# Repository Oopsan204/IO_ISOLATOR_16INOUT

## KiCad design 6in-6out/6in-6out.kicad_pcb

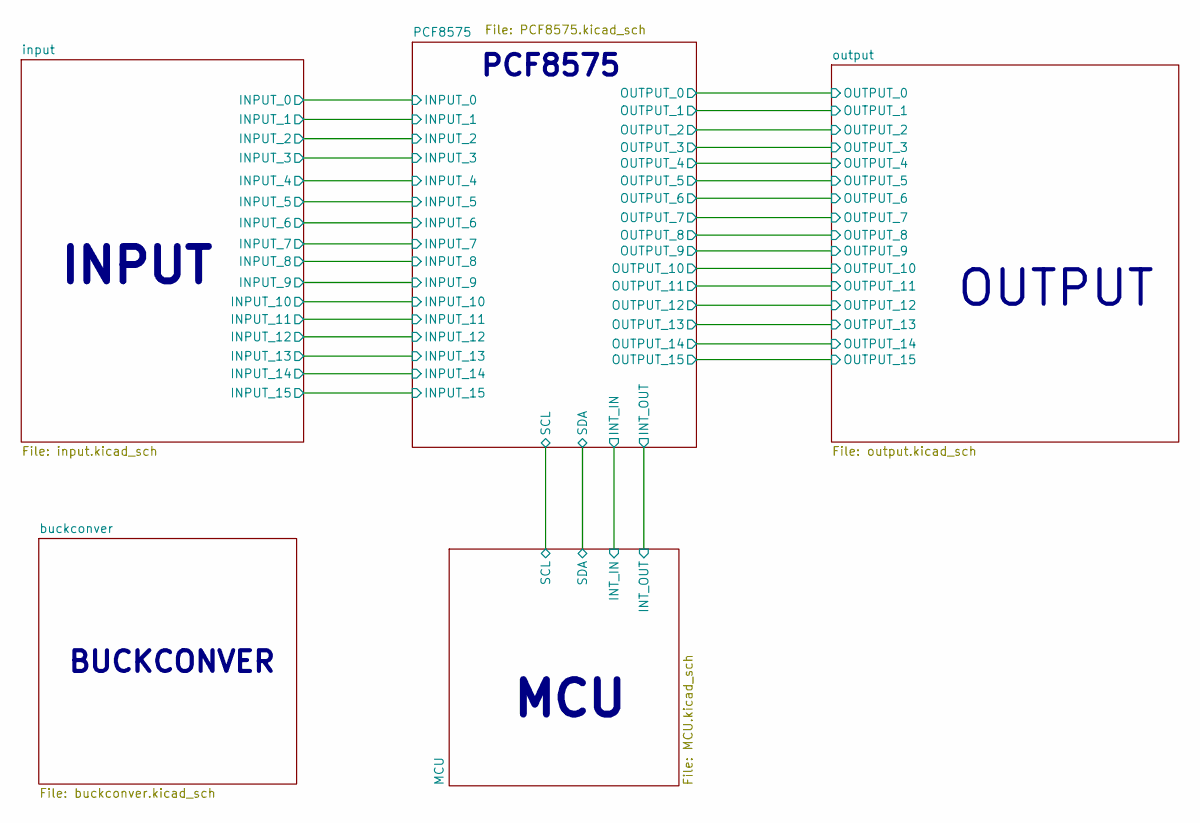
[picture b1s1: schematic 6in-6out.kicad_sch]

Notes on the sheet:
MCU
OUTPUT
PCF8575
INPUT
BUCKCONVER

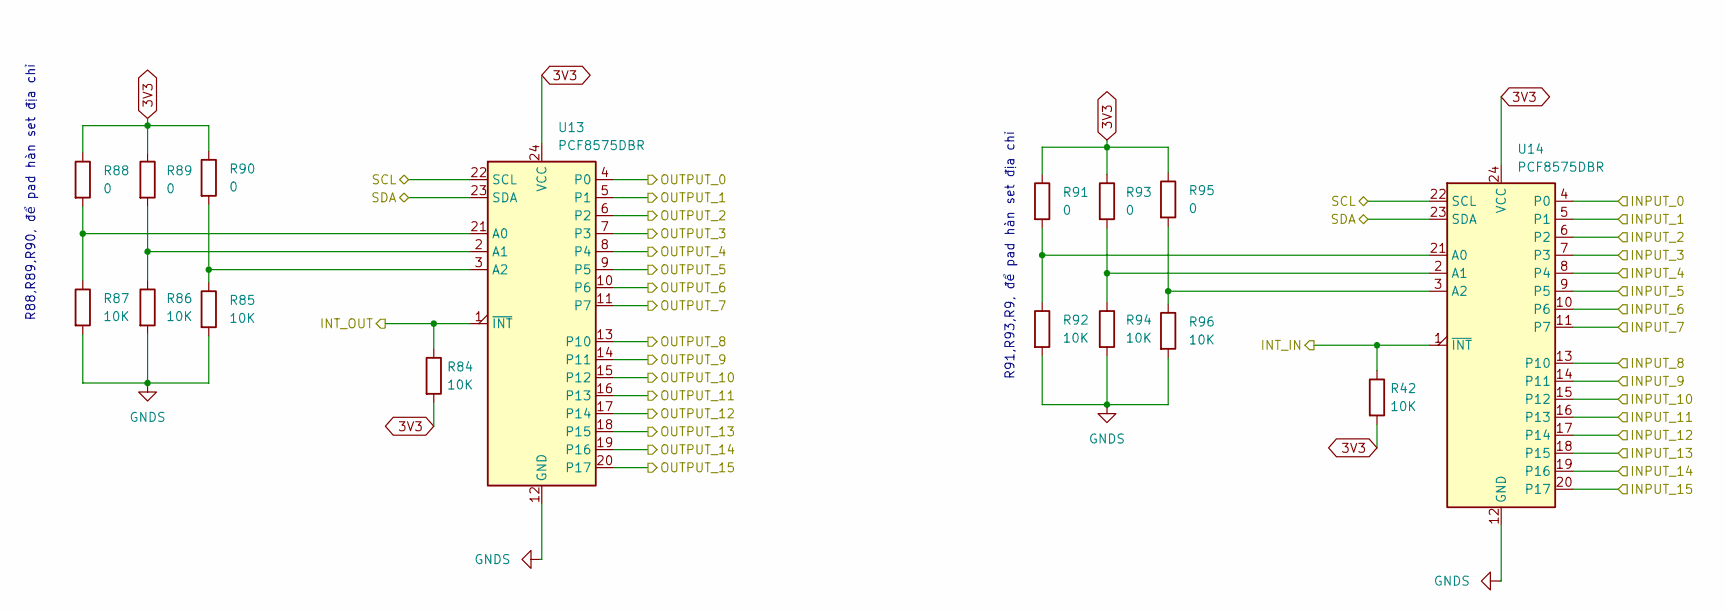
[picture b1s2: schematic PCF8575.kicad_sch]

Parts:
R42, R84, R85, R86, R87, R92, R94, R96: 10K; R_0603_1608Metric_Pad0.98x0.95mm_HandSolder
R88, R89, R90, R91, R93, R95: 0; R_0603_1608Metric_Pad0.98x0.95mm_HandSolder
U13, U14: PCF8575DBR; SSOP-24_5.3x8.2mm_P0.65mm

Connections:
3V3: R42.2, R84.2, R88.1, R89.1, R90.1, R91.1, R93.1, R95.1, U13.24 (VCC), U14.24 (VCC); also elsewhere on the board
/MCU/INT_IN: R42.1, U14.1 (~INT); also elsewhere on the board
/MCU/INT_OUT: R84.1, U13.1 (~INT); also elsewhere on the board
/MCU/SCL: U13.22 (SCL), U14.22 (SCL); also elsewhere on the board
/MCU/SDA: U13.23 (SDA), U14.23 (SDA); also elsewhere on the board
/PCF8575/INPUT_0: U14.4 (P0); also elsewhere on the board
/PCF8575/INPUT_1: U14.5 (P1); also elsewhere on the board
/PCF8575/INPUT_2: U14.6 (P2); also elsewhere on the board
/PCF8575/INPUT_3: U14.7 (P3); also elsewhere on the board
/PCF8575/INPUT_4: U14.8 (P4); also elsewhere on the board
/PCF8575/INPUT_5: U14.9 (P5); also elsewhere on the board
/PCF8575/INPUT_6: U14.10 (P6); also elsewhere on the board
/PCF8575/INPUT_7: U14.11 (P7); also elsewhere on the board
/PCF8575/INPUT_8: U14.13 (P10); also elsewhere on the board
/PCF8575/INPUT_9: U14.14 (P11); also elsewhere on the board
/PCF8575/INPUT_10: U14.15 (P12); also elsewhere on the board
/PCF8575/INPUT_11: U14.16 (P13); also elsewhere on the board
/PCF8575/INPUT_12: U14.17 (P14); also elsewhere on the board
/PCF8575/INPUT_13: U14.18 (P15); also elsewhere on the board
/PCF8575/INPUT_14: U14.19 (P16); also elsewhere on the board
/PCF8575/INPUT_15: U14.20 (P17); also elsewhere on the board
/PCF8575/OUTPUT_0: U13.4 (P0); also elsewhere on the board
/PCF8575/OUTPUT_1: U13.5 (P1); also elsewhere on the board
/PCF8575/OUTPUT_2: U13.6 (P2); also elsewhere on the board
/PCF8575/OUTPUT_3: U13.7 (P3); also elsewhere on the board
/PCF8575/OUTPUT_4: U13.8 (P4); also elsewhere on the board
/PCF8575/OUTPUT_5: U13.9 (P5); also elsewhere on the board
/PCF8575/OUTPUT_6: U13.10 (P6); also elsewhere on the board
/PCF8575/OUTPUT_7: U13.11 (P7); also elsewhere on the board
/PCF8575/OUTPUT_8: U13.13 (P10); also elsewhere on the board
/PCF8575/OUTPUT_9: U13.14 (P11); also elsewhere on the board
/PCF8575/OUTPUT_10: U13.15 (P12); also elsewhere on the board
/PCF8575/OUTPUT_11: U13.16 (P13); also elsewhere on the board
/PCF8575/OUTPUT_12: U13.17 (P14); also elsewhere on the board
/PCF8575/OUTPUT_13: U13.18 (P15); also elsewhere on the board
/PCF8575/OUTPUT_14: U13.19 (P16); also elsewhere on the board
/PCF8575/OUTPUT_15: U13.20 (P17); also elsewhere on the board
GNDS: R85.2, R86.2, R87.2, R92.2, R94.2, R96.2, U13.12 (GND), U14.12 (GND); also elsewhere on the board
unnamed: R87.1, R88.2, U13.21 (A0)
unnamed: R86.1, R89.2, U13.2 (A1)
unnamed: R85.1, R90.2, U13.3 (A2)
unnamed: R91.2, R92.1, U14.21 (A0)
unnamed: R93.2, R94.1, U14.2 (A1)
unnamed: R95.2, R96.1, U14.3 (A2)

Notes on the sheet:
R88,R89,R90, để pad hàn set địa chỉ
R91,R93,R9, để pad hàn set địa chỉ

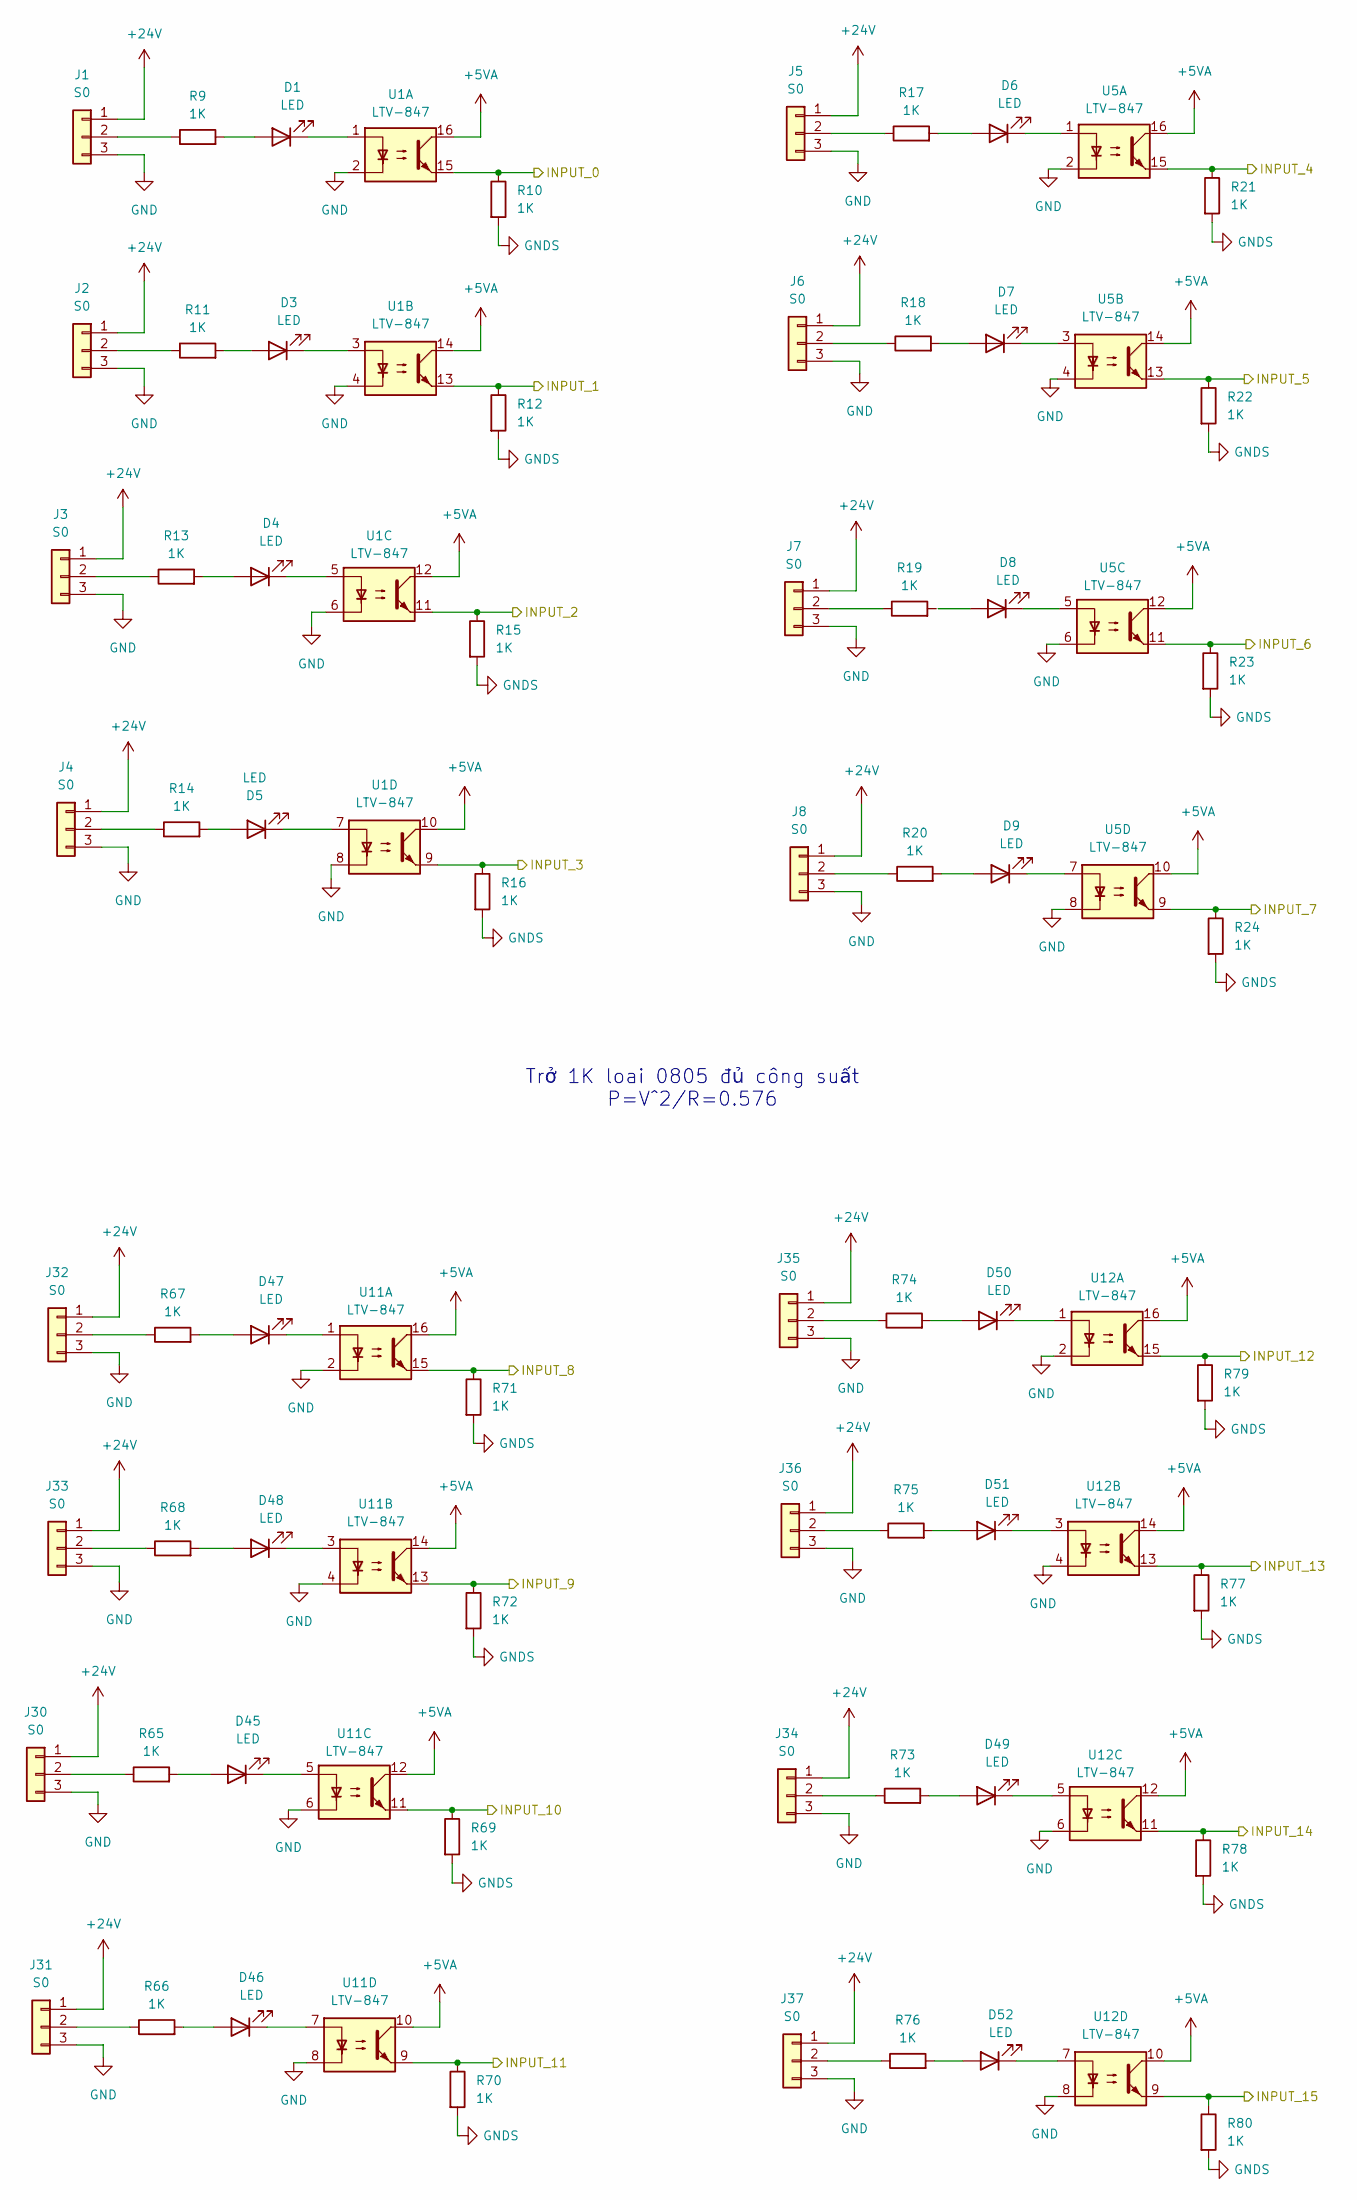
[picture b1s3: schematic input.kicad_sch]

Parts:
D1, D3, D4, D5, D6, D7, D8, D9, D45, D46, D47, D48, D49, D50, D51, D52: LED; LED_0603_1608Metric_Pad1.05x0.95mm_HandSolder
J1, J2, J3, J4, J5, J6, J7, J8, J30, J31, J32, J33, J34, J35, J36, J37: S0; JST 3
R9, R10, R11, R12, R13, R14, R15, R16, R17, R18, R19, R20, R21, R22, R23, R24, R65, R66, R67, R68, R69, R70, R71, R72, R73, R74, R75, R76, R77, R78, R79, R80: 1K; R_0805_2012Metric_Pad1.20x1.40mm_HandSolder
U1, U5, U11, U12: LTV-847; DIP-16_W7.62mm

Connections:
+5VA: U1.10, U1.12, U1.14, U1.16, U5.10, U5.12, U5.14, U5.16, U11.10, U11.12, U11.14, U11.16, U12.10, U12.12, U12.14, U12.16; also elsewhere on the board
+24V: J1.1, J2.1, J3.1, J4.1, J5.1, J6.1, J7.1, J8.1, J30.1, J31.1, J32.1, J33.1, J34.1, J35.1, J36.1, J37.1; also elsewhere on the board
/PCF8575/INPUT_0: R10.1, U1.15; also elsewhere on the board
/PCF8575/INPUT_1: R12.1, U1.13; also elsewhere on the board
/PCF8575/INPUT_2: R15.1, U1.11; also elsewhere on the board
/PCF8575/INPUT_3: R16.1, U1.9; also elsewhere on the board
/PCF8575/INPUT_4: R21.1, U5.15; also elsewhere on the board
/PCF8575/INPUT_5: R22.1, U5.13; also elsewhere on the board
/PCF8575/INPUT_6: R23.1, U5.11; also elsewhere on the board
/PCF8575/INPUT_7: R24.1, U5.9; also elsewhere on the board
/PCF8575/INPUT_8: R71.1, U11.15; also elsewhere on the board
/PCF8575/INPUT_9: R72.1, U11.13; also elsewhere on the board
/PCF8575/INPUT_10: R69.1, U11.11; also elsewhere on the board
/PCF8575/INPUT_11: R70.1, U11.9; also elsewhere on the board
/PCF8575/INPUT_12: R79.1, U12.15; also elsewhere on the board
/PCF8575/INPUT_13: R77.1, U12.13; also elsewhere on the board
/PCF8575/INPUT_14: R78.1, U12.11; also elsewhere on the board
/PCF8575/INPUT_15: R80.1, U12.9; also elsewhere on the board
GND: J1.3, J2.3, J3.3, J4.3, J5.3, J6.3, J7.3, J8.3, J30.3, J31.3, J32.3, J33.3, J34.3, J35.3, J36.3, J37.3, U1.2, U1.4, U1.6, U1.8, U5.2, U5.4, U5.6, U5.8, U11.2, U11.4, U11.6, U11.8, U12.2, U12.4, U12.6, U12.8; also elsewhere on the board
GNDS: R10.2, R12.2, R15.2, R16.2, R21.2, R22.2, R23.2, R24.2, R69.2, R70.2, R71.2, R72.2, R77.2, R78.2, R79.2, R80.2; also elsewhere on the board
unnamed: D1.2 (A), R9.2
unnamed: D1.1 (K), U1.1
unnamed: D3.2 (A), R11.2
unnamed: D3.1 (K), U1.3
unnamed: D4.2 (A), R13.2
unnamed: D4.1 (K), U1.5
unnamed: D5.2 (A), R14.2
unnamed: D5.1 (K), U1.7
unnamed: D6.2 (A), R17.2
unnamed: D6.1 (K), U5.1
unnamed: D7.2 (A), R18.2
unnamed: D7.1 (K), U5.3
unnamed: D8.1 (K), U5.5
unnamed: D9.2 (A), R20.2
unnamed: D9.1 (K), U5.7
unnamed: D45.2 (A), R65.2
unnamed: D45.1 (K), U11.5
unnamed: D46.2 (A), R66.2
unnamed: D46.1 (K), U11.7
unnamed: D47.2 (A), R67.2
unnamed: D47.1 (K), U11.1
unnamed: D48.2 (A), R68.2
unnamed: D48.1 (K), U11.3
unnamed: D49.2 (A), R73.2
unnamed: D49.1 (K), U12.5
unnamed: D50.2 (A), R74.2
unnamed: D50.1 (K), U12.1
unnamed: D51.2 (A), R75.2
unnamed: D51.1 (K), U12.3
unnamed: D52.2 (A), R76.2
unnamed: D52.1 (K), U12.7
unnamed: J1.2, R9.1
unnamed: J2.2, R11.1
unnamed: J3.2, R13.1
unnamed: J4.2, R14.1
unnamed: J5.2, R17.1
unnamed: J6.2, R18.1
unnamed: J7.2, R19.1
unnamed: J8.2, R20.1
unnamed: J30.2, R65.1
unnamed: J31.2, R66.1
unnamed: J32.2, R67.1
unnamed: J33.2, R68.1
unnamed: J34.2, R73.1
unnamed: J35.2, R74.1
unnamed: J36.2, R75.1
unnamed: J37.2, R76.1

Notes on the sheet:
Trở 1K loai 0805 đủ công suất P=V^2/R=0.576

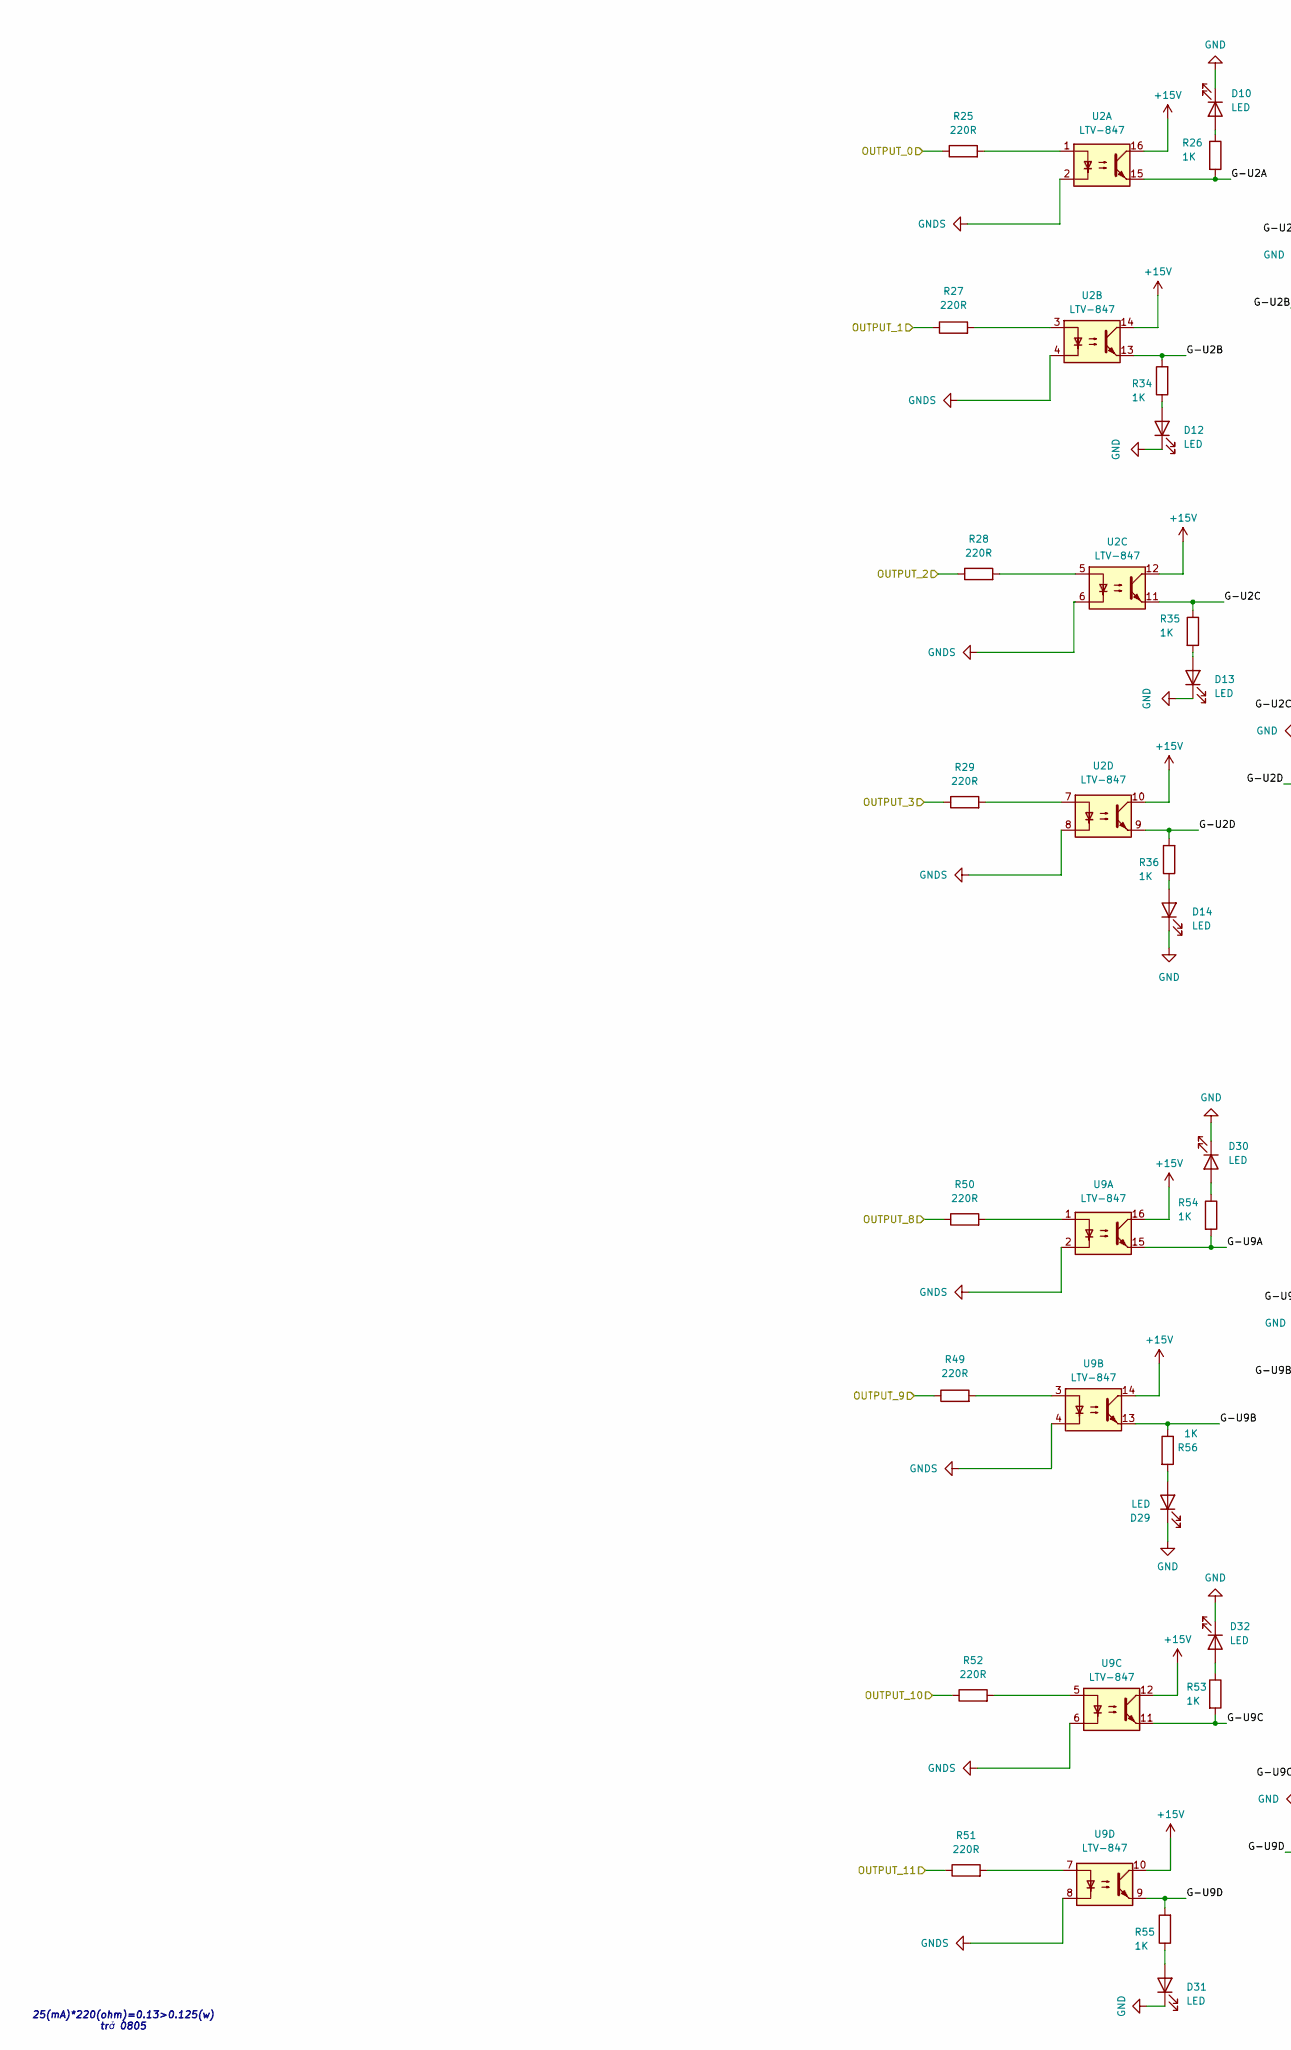
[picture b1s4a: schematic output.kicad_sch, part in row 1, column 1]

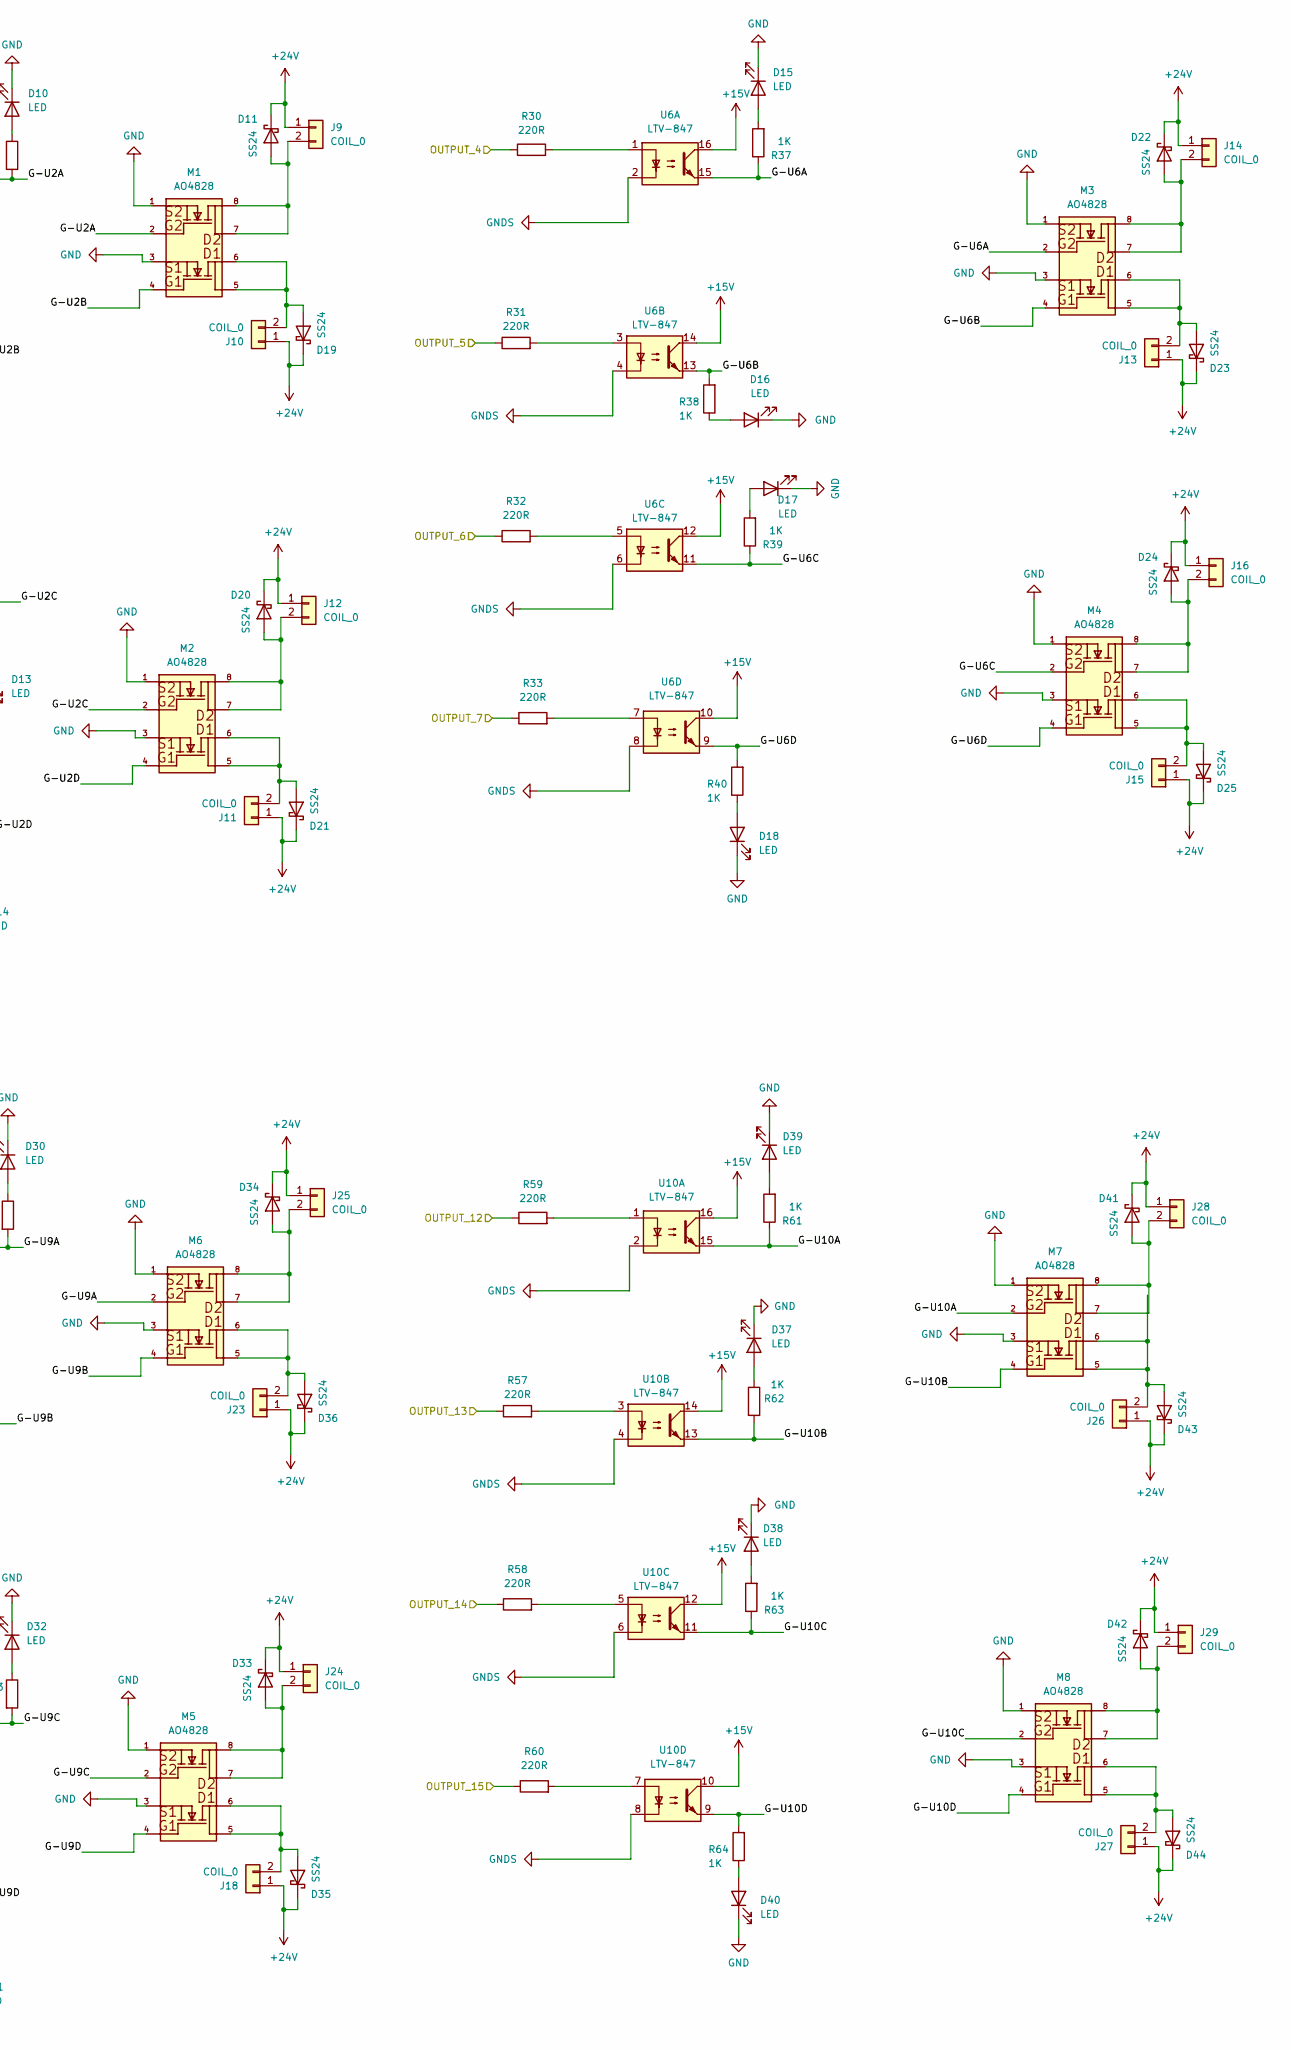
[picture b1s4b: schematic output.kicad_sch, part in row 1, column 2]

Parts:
D10, D12, D13, D14, D15, D16, D17, D18, D29, D30, D31, D32, D37, D38, D39, D40: LED; LED_0603_1608Metric_Pad1.05x0.95mm_HandSolder
D11, D19, D20, D21, D22, D23, D24, D25, D33, D34, D35, D36, D41, D42, D43, D44: SS24; D_2010_5025Metric_Pad1.52x2.65mm_HandSolder
J9, J10, J11, J12, J13, J14, J15, J16, J18, J23, J24, J25, J26, J27, J28, J29: COIL_0; JST 2
M1, M2, M3, M4, M5, M6, M7, M8: AO4828; SOIC-8
R25, R27, R28, R29, R30, R31, R32, R33, R49, R50, R51, R52, R57, R58, R59, R60: 220R; R_0603_1608Metric_Pad0.98x0.95mm_HandSolder
R26, R34, R35, R36, R37, R38, R39, R40, R53, R54, R55, R56, R61, R62, R63, R64: 1K; R_0805_2012Metric_Pad1.20x1.40mm_HandSolder
U2, U6, U9, U10: LTV-847; DIP-16_W7.62mm

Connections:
+15V: U2.10, U2.12, U2.14, U2.16, U6.10, U6.12, U6.14, U6.16, U9.10, U9.12, U9.14, U9.16, U10.10, U10.12, U10.14, U10.16; also elsewhere on the board
+24V: D11.1 (K), D19.1 (K), D20.1 (K), D21.1 (K), D22.1 (K), D23.1 (K), D24.1 (K), D25.1 (K), D33.1 (K), D34.1 (K), D35.1 (K), D36.1 (K), D41.1 (K), D42.1 (K), D43.1 (K), D44.1 (K), J9.1, J10.1, J11.1, J12.1, J13.1, J14.1, J15.1, J16.1, J18.1, J23.1, J24.1, J25.1, J26.1, J27.1, J28.1, J29.1; also elsewhere on the board
/PCF8575/OUTPUT_0: R25.1; also elsewhere on the board
/PCF8575/OUTPUT_1: R27.1; also elsewhere on the board
/PCF8575/OUTPUT_2: R28.1; also elsewhere on the board
/PCF8575/OUTPUT_3: R29.1; also elsewhere on the board
/PCF8575/OUTPUT_4: R30.1; also elsewhere on the board
/PCF8575/OUTPUT_5: R31.1; also elsewhere on the board
/PCF8575/OUTPUT_6: R32.1; also elsewhere on the board
/PCF8575/OUTPUT_7: R33.1; also elsewhere on the board
/PCF8575/OUTPUT_8: R50.1; also elsewhere on the board
/PCF8575/OUTPUT_9: R49.1; also elsewhere on the board
/PCF8575/OUTPUT_10: R52.1; also elsewhere on the board
/PCF8575/OUTPUT_11: R51.1; also elsewhere on the board
/PCF8575/OUTPUT_12: R59.1; also elsewhere on the board
/PCF8575/OUTPUT_13: R57.1; also elsewhere on the board
/PCF8575/OUTPUT_14: R58.1; also elsewhere on the board
/PCF8575/OUTPUT_15: R60.1; also elsewhere on the board
/output/G-U2A: M1.2, R26.2, U2.15
/output/G-U2B: M1.4, R34.2, U2.13
/output/G-U2C: M2.2, R35.1, U2.11
/output/G-U2D: M2.4, R36.2, U2.9
/output/G-U6A: M3.2, R37.1, U6.15
/output/G-U6B: M3.4, R38.2, U6.13
/output/G-U6C: M4.2, R39.1, U6.11
/output/G-U6D: M4.4, R40.2, U6.9
/output/G-U9A: M6.2, R54.2, U9.15
/output/G-U9B: M6.4, R56.1, U9.13
/output/G-U9C: M5.2, R53.2, U9.11
/output/G-U9D: M5.4, R55.2, U9.9
/output/G-U10A: M7.2, R61.1, U10.15
/output/G-U10B: M7.4, R62.2, U10.13
/output/G-U10C: M8.2, R63.1, U10.11
/output/G-U10D: M8.4, R64.2, U10.9
GND: D10.1 (K), D12.1 (K), D13.1 (K), D14.1 (K), D15.1 (K), D16.1 (K), D17.1 (K), D18.1 (K), D29.1 (K), D30.1 (K), D31.1 (K), D32.1 (K), D37.1 (K), D38.1 (K), D39.1 (K), D40.1 (K), M1.1, M1.3, M2.1, M2.3, M3.1, M3.3, M4.1, M4.3, M5.1, M5.3, M6.1, M6.3, M7.1, M7.3, M8.1, M8.3; also elsewhere on the board
GNDS: U2.2, U2.4, U2.6, U2.8, U6.2, U6.4, U6.6, U6.8, U9.2, U9.4, U9.6, U9.8, U10.2, U10.4, U10.6, U10.8; also elsewhere on the board
unnamed: D10.2 (A), R26.1
unnamed: D11.2 (A), J9.2, M1.7, M1.8
unnamed: D12.2 (A), R34.1
unnamed: D13.2 (A), R35.2
unnamed: D14.2 (A), R36.1
unnamed: D15.2 (A), R37.2
unnamed: D16.2 (A), R38.1
unnamed: D17.2 (A), R39.2
unnamed: D18.2 (A), R40.1
unnamed: D19.2 (A), J10.2, M1.5, M1.6
unnamed: D20.2 (A), J12.2, M2.7, M2.8
unnamed: D21.2 (A), J11.2, M2.5, M2.6
unnamed: D22.2 (A), J14.2, M3.7, M3.8
unnamed: D23.2 (A), J13.2, M3.5, M3.6
unnamed: D24.2 (A), J16.2, M4.7, M4.8
unnamed: D25.2 (A), J15.2, M4.5, M4.6
unnamed: D29.2 (A), R56.2
unnamed: D30.2 (A), R54.1
unnamed: D31.2 (A), R55.1
unnamed: D32.2 (A), R53.1
unnamed: D33.2 (A), J24.2, M5.7, M5.8
unnamed: D34.2 (A), J25.2, M6.7, M6.8
unnamed: D35.2 (A), J18.2, M5.5, M5.6
unnamed: D36.2 (A), J23.2, M6.5, M6.6
unnamed: D37.2 (A), R62.1
unnamed: D38.2 (A), R63.2
unnamed: D39.2 (A), R61.2
unnamed: D40.2 (A), R64.1
unnamed: D41.2 (A), J28.2, M7.7, M7.8
unnamed: D42.2 (A), J29.2, M8.7, M8.8
unnamed: D43.2 (A), J26.2, M7.5, M7.6
unnamed: D44.2 (A), J27.2, M8.5, M8.6
unnamed: R25.2, U2.1
unnamed: R27.2, U2.3
unnamed: R28.2, U2.5
unnamed: R29.2, U2.7
unnamed: R30.2, U6.1
unnamed: R31.2, U6.3
unnamed: R32.2, U6.5
unnamed: R33.2, U6.7
unnamed: R49.2, U9.3
unnamed: R50.2, U9.1
unnamed: R51.2, U9.7
unnamed: R52.2, U9.5
unnamed: R57.2, U10.3
unnamed: R58.2, U10.5
unnamed: R59.2, U10.1
unnamed: R60.2, U10.7

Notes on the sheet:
25(mA)*220(ohm)=0.13>0.125(w) trở 0805

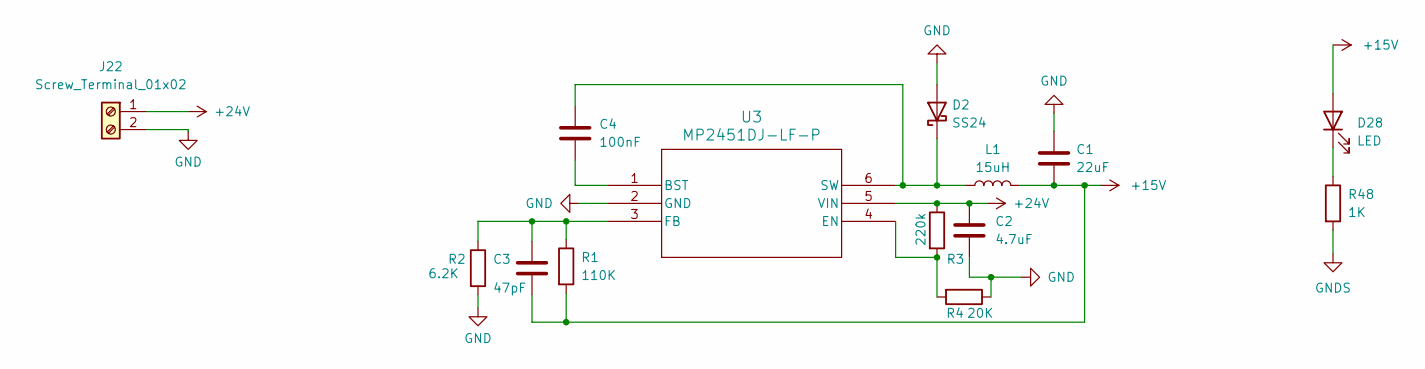
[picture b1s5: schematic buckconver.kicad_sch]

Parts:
C1: 22uF; C_0201_0603Metric_Pad0.64x0.40mm_HandSolder
C2: 4.7uF; C_0805_2012Metric_Pad1.18x1.45mm_HandSolder
C3: 47pF; R_0805_2012Metric_Pad1.20x1.40mm_HandSolder
C4: 100nF; C_0603_1608Metric_Pad1.08x0.95mm_HandSolder
D2: SS24; D_2010_5025Metric_Pad1.52x2.65mm_HandSolder
D28: LED; LED_0603_1608Metric_Pad1.05x0.95mm_HandSolder
J22: Screw_Terminal_01x02; JST_VH_B2P-VH-B_1x02_P3.96mm_Vertical
L1: 15uH; L_7.3x7.3_H4.5
R1: 110K; R_0805_2012Metric_Pad1.20x1.40mm_HandSolder
R2: 6.2K; R_0805_2012Metric_Pad1.20x1.40mm_HandSolder
R3: 220k; R_0805_2012Metric_Pad1.20x1.40mm_HandSolder
R4: 20K; R_0805_2012Metric_Pad1.20x1.40mm_HandSolder
R48: 1K; R_0805_2012Metric_Pad1.20x1.40mm_HandSolder
U3: MP2451DJ-LF-P; TSOT23-6_MP2451_MNP

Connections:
+15V: C1.2, C3.2, D28.2 (A), L1.2, R1.2; also elsewhere on the board
+24V: C2.1, J22.1, R3.1, U3.5 (VIN); also elsewhere on the board
GND: C1.1, C2.2, D2.2 (A), J22.2, R2.2, R4.1, U3.2 (GND); also elsewhere on the board
GNDS: R48.2; also elsewhere on the board
unnamed: C4.2, D2.1 (K), L1.1, U3.6 (SW)
unnamed: D28.1 (K), R48.1
unnamed: C4.1, U3.1 (BST)
unnamed: R3.2, R4.2, U3.4 (EN)
unnamed: C3.1, R1.1, R2.1, U3.3 (FB)
